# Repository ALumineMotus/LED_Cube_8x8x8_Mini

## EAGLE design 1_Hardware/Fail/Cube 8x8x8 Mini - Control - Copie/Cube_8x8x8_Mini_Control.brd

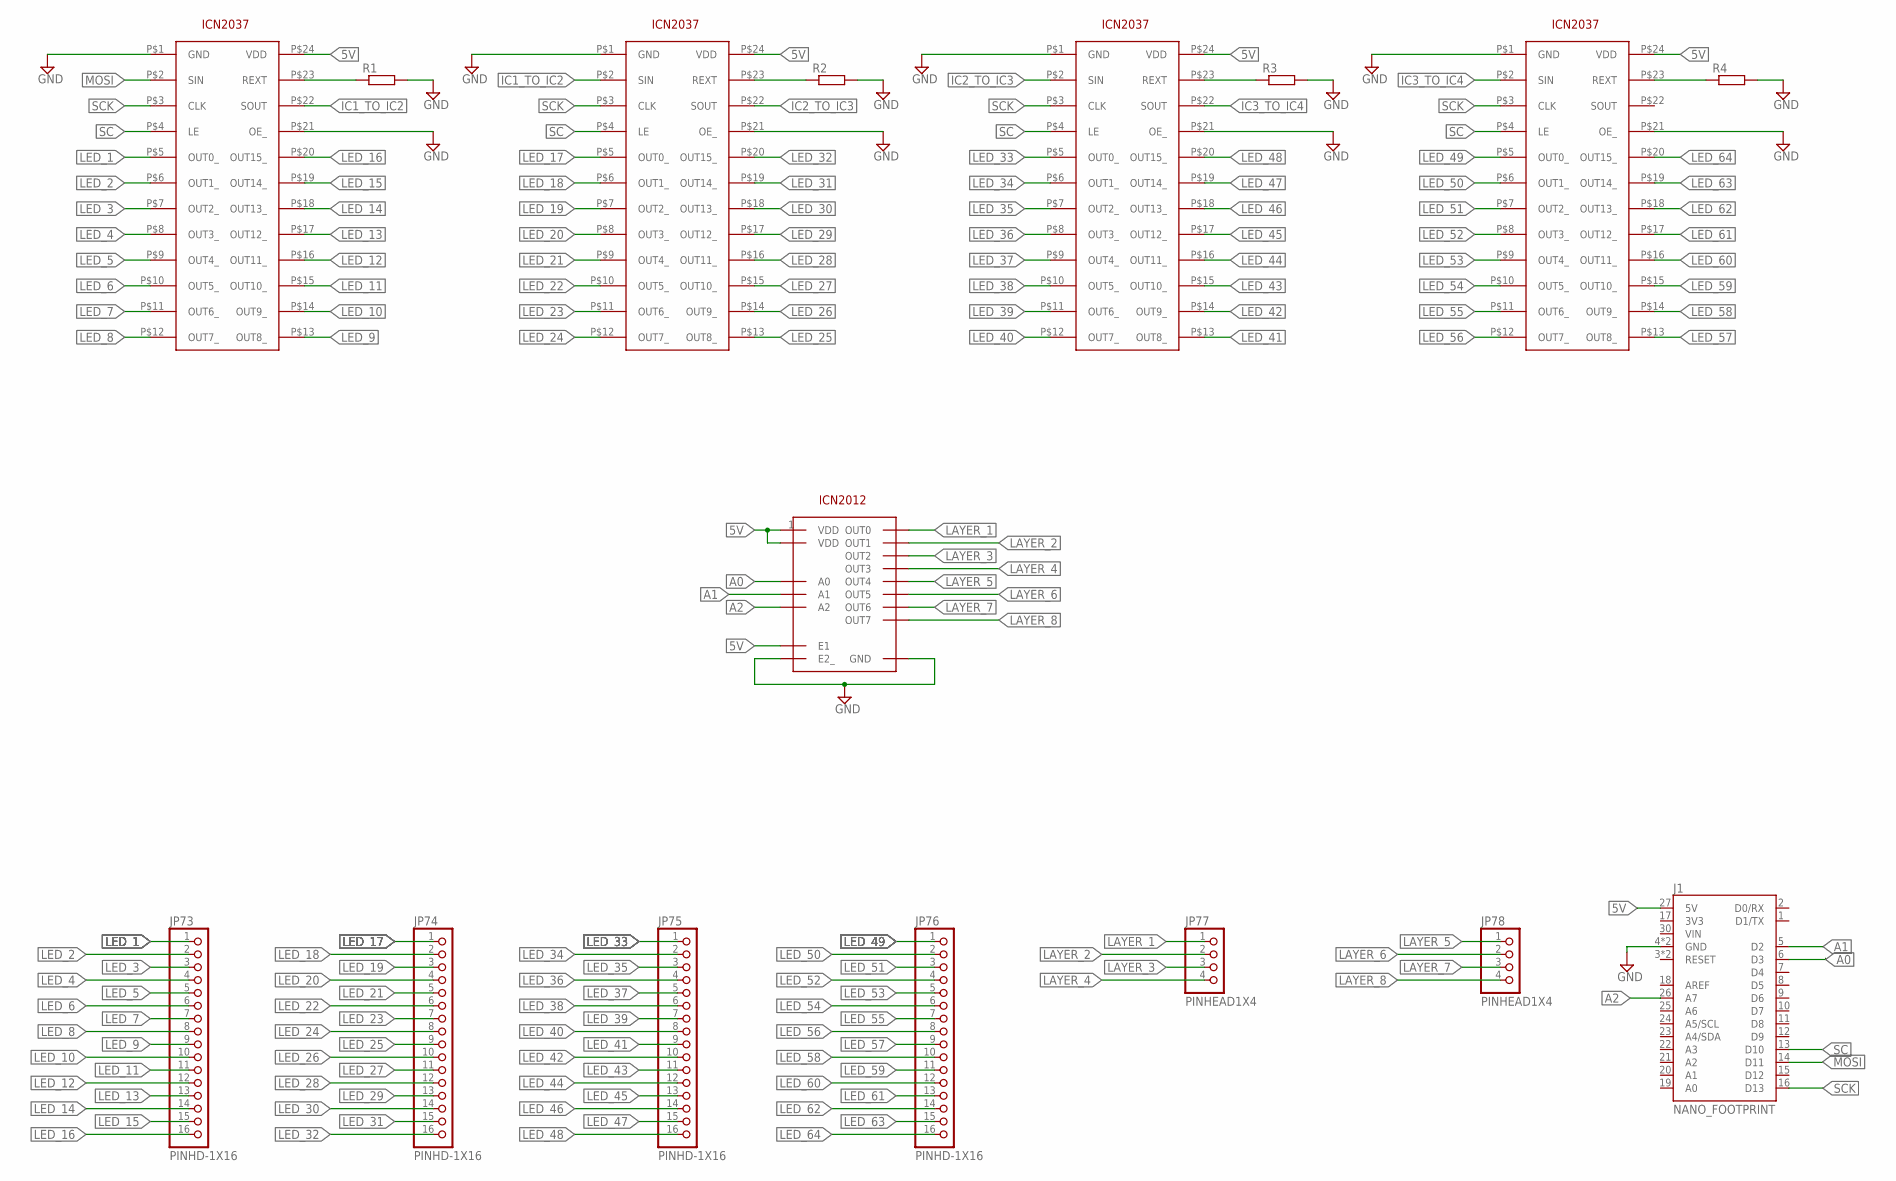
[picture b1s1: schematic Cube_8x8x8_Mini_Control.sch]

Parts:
J1: NANO_FOOTPRINT; NANO
JP73, JP74, JP75, JP76: PINHD-1X16; 2X16
JP77, JP78: PINHEAD1X4; 2X04
R1, R2, R3, R4: R-EU_R1206; R1206
U1, U2, U3, U4: ICN2037; SSOP24-P-150-0.635
U5: ICN2012; SOP16

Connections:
5V: J1.27 (5V), U1.P$24 (VDD), U2.P$24 (VDD), U3.P$24 (VDD), U4.P$24 (VDD), U5.1 (VDD), U5.7 (E1), U5.9 (VDD)
A0: J1.6 (D3), U5.15 (A0)
A1: J1.5 (D2), U5.16 (A1)
A2: J1.26 (A7), U5.2 (A2)
GND: J1.4 (GND), J1.29 (GND), R1.2, R2.2, R3.2, R4.2, U1.P$1 (GND), U1.P$21 (OE_), U2.P$1 (GND), U2.P$21 (OE_), U3.P$1 (GND), U3.P$21 (OE_), U4.P$1 (GND), U4.P$21 (OE_), U5.8 (GND), U5.10 (E2_)
IC1_TO_IC2: U1.P$22 (SOUT), U2.P$2 (SIN)
IC2_TO_IC3: U2.P$22 (SOUT), U3.P$2 (SIN)
IC3_TO_IC4: U3.P$22 (SOUT), U4.P$2 (SIN)
LAYER_1: JP77.1, U5.3 (OUT0)
LAYER_2: JP77.2, U5.4 (OUT1)
LAYER_3: JP77.3, U5.5 (OUT2)
LAYER_4: JP77.4, U5.6 (OUT3)
LAYER_5: JP78.1, U5.11 (OUT4)
LAYER_6: JP78.2, U5.12 (OUT5)
LAYER_7: JP78.3, U5.13 (OUT6)
LAYER_8: JP78.4, U5.14 (OUT7)
LED_1: JP73.1, U1.P$5 (OUT0_)
LED_2: JP73.2, U1.P$6 (OUT1_)
LED_3: JP73.3, U1.P$7 (OUT2_)
LED_4: JP73.4, U1.P$8 (OUT3_)
LED_5: JP73.5, U1.P$9 (OUT4_)
LED_6: JP73.6, U1.P$10 (OUT5_)
LED_7: JP73.7, U1.P$11 (OUT6_)
LED_8: JP73.8, U1.P$12 (OUT7_)
LED_9: JP73.9, U1.P$13 (OUT8_)
LED_10: JP73.10, U1.P$14 (OUT9_)
LED_11: JP73.11, U1.P$15 (OUT10_)
LED_12: JP73.12, U1.P$16 (OUT11_)
LED_13: JP73.13, U1.P$17 (OUT12_)
LED_14: JP73.14, U1.P$18 (OUT13_)
LED_15: JP73.15, U1.P$19 (OUT14_)
LED_16: JP73.16, U1.P$20 (OUT15_)
LED_17: JP74.1, U2.P$5 (OUT0_)
LED_18: JP74.2, U2.P$6 (OUT1_)
LED_19: JP74.3, U2.P$7 (OUT2_)
LED_20: JP74.4, U2.P$8 (OUT3_)
LED_21: JP74.5, U2.P$9 (OUT4_)
LED_22: JP74.6, U2.P$10 (OUT5_)
LED_23: JP74.7, U2.P$11 (OUT6_)
LED_24: JP74.8, U2.P$12 (OUT7_)
LED_25: JP74.9, U2.P$13 (OUT8_)
LED_26: JP74.10, U2.P$14 (OUT9_)
LED_27: JP74.11, U2.P$15 (OUT10_)
LED_28: JP74.12, U2.P$16 (OUT11_)
LED_29: JP74.13, U2.P$17 (OUT12_)
LED_30: JP74.14, U2.P$18 (OUT13_)
LED_31: JP74.15, U2.P$19 (OUT14_)
LED_32: JP74.16, U2.P$20 (OUT15_)
LED_33: JP75.1, U3.P$5 (OUT0_)
LED_34: JP75.2, U3.P$6 (OUT1_)
LED_35: JP75.3, U3.P$7 (OUT2_)
LED_36: JP75.4, U3.P$8 (OUT3_)
LED_37: JP75.5, U3.P$9 (OUT4_)
LED_38: JP75.6, U3.P$10 (OUT5_)
LED_39: JP75.7, U3.P$11 (OUT6_)
LED_40: JP75.8, U3.P$12 (OUT7_)
LED_41: JP75.9, U3.P$13 (OUT8_)
LED_42: JP75.10, U3.P$14 (OUT9_)
LED_43: JP75.11, U3.P$15 (OUT10_)
LED_44: JP75.12, U3.P$16 (OUT11_)
LED_45: JP75.13, U3.P$17 (OUT12_)
LED_46: JP75.14, U3.P$18 (OUT13_)
LED_47: JP75.15, U3.P$19 (OUT14_)
LED_48: JP75.16, U3.P$20 (OUT15_)
LED_49: JP76.1, U4.P$5 (OUT0_)
LED_50: JP76.2, U4.P$6 (OUT1_)
LED_51: JP76.3, U4.P$7 (OUT2_)
LED_52: JP76.4, U4.P$8 (OUT3_)
LED_53: JP76.5, U4.P$9 (OUT4_)
LED_54: JP76.6, U4.P$10 (OUT5_)
LED_55: JP76.7, U4.P$11 (OUT6_)
LED_56: JP76.8, U4.P$12 (OUT7_)
LED_57: JP76.9, U4.P$13 (OUT8_)
LED_58: JP76.10, U4.P$14 (OUT9_)
LED_59: JP76.11, U4.P$15 (OUT10_)
LED_60: JP76.12, U4.P$16 (OUT11_)
LED_61: JP76.13, U4.P$17 (OUT12_)
LED_62: JP76.14, U4.P$18 (OUT13_)
LED_63: JP76.15, U4.P$19 (OUT14_)
LED_64: JP76.16, U4.P$20 (OUT15_)
MOSI: J1.14 (D11), U1.P$2 (SIN)
unnamed: R1.1, U1.P$23 (REXT)
unnamed: R2.1, U2.P$23 (REXT)
unnamed: R3.1, U3.P$23 (REXT)
unnamed: R4.1, U4.P$23 (REXT)
SC: J1.13 (D10), U1.P$4 (LE), U2.P$4 (LE), U3.P$4 (LE), U4.P$4 (LE)
SCK: J1.16 (D13), U1.P$3 (CLK), U2.P$3 (CLK), U3.P$3 (CLK), U4.P$3 (CLK)

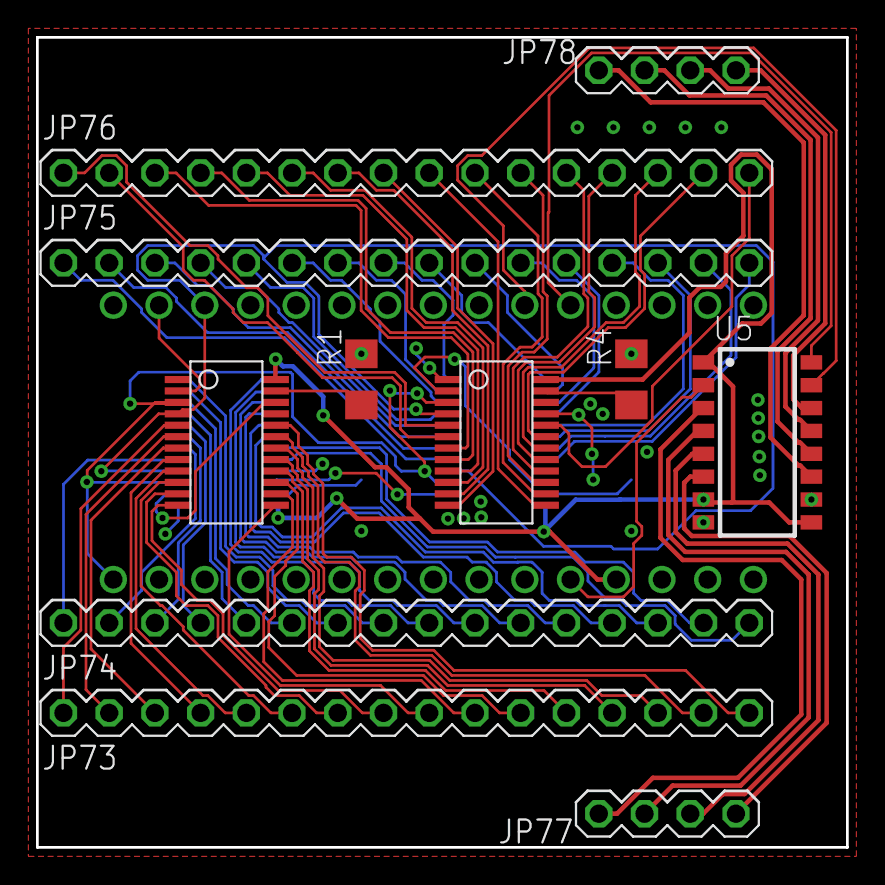
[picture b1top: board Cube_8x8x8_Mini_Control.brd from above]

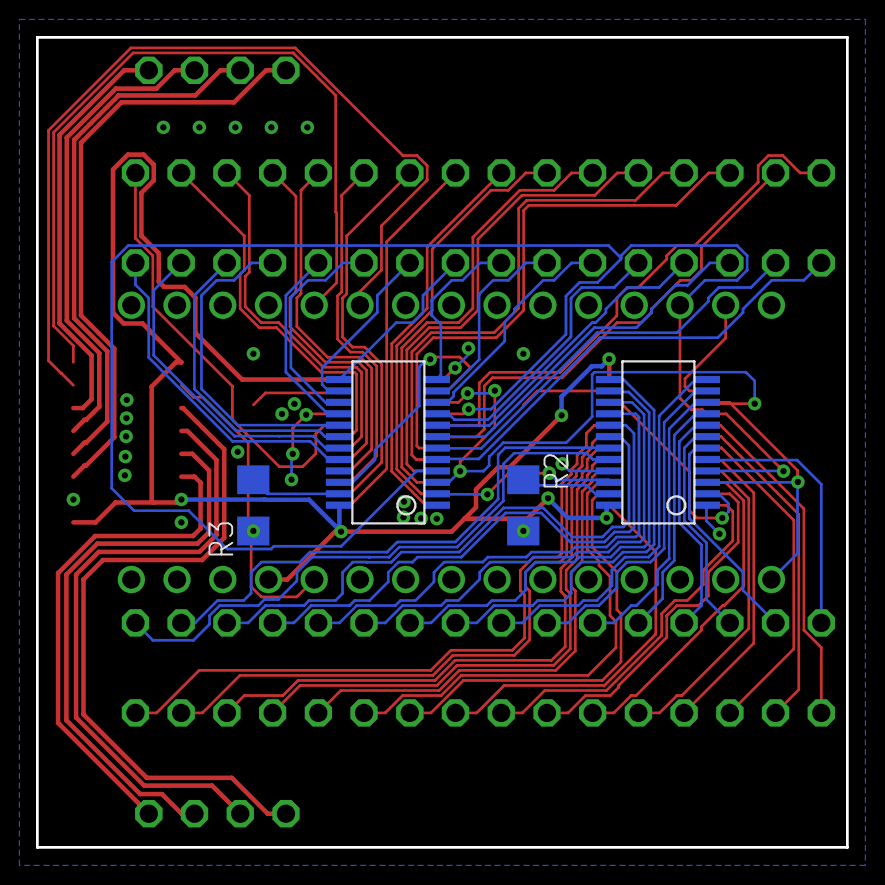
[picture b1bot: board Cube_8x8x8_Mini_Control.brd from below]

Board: 2 copper layers, 45.0 x 45.0 mm, 16 parts (4 on the bottom side), 87 nets.

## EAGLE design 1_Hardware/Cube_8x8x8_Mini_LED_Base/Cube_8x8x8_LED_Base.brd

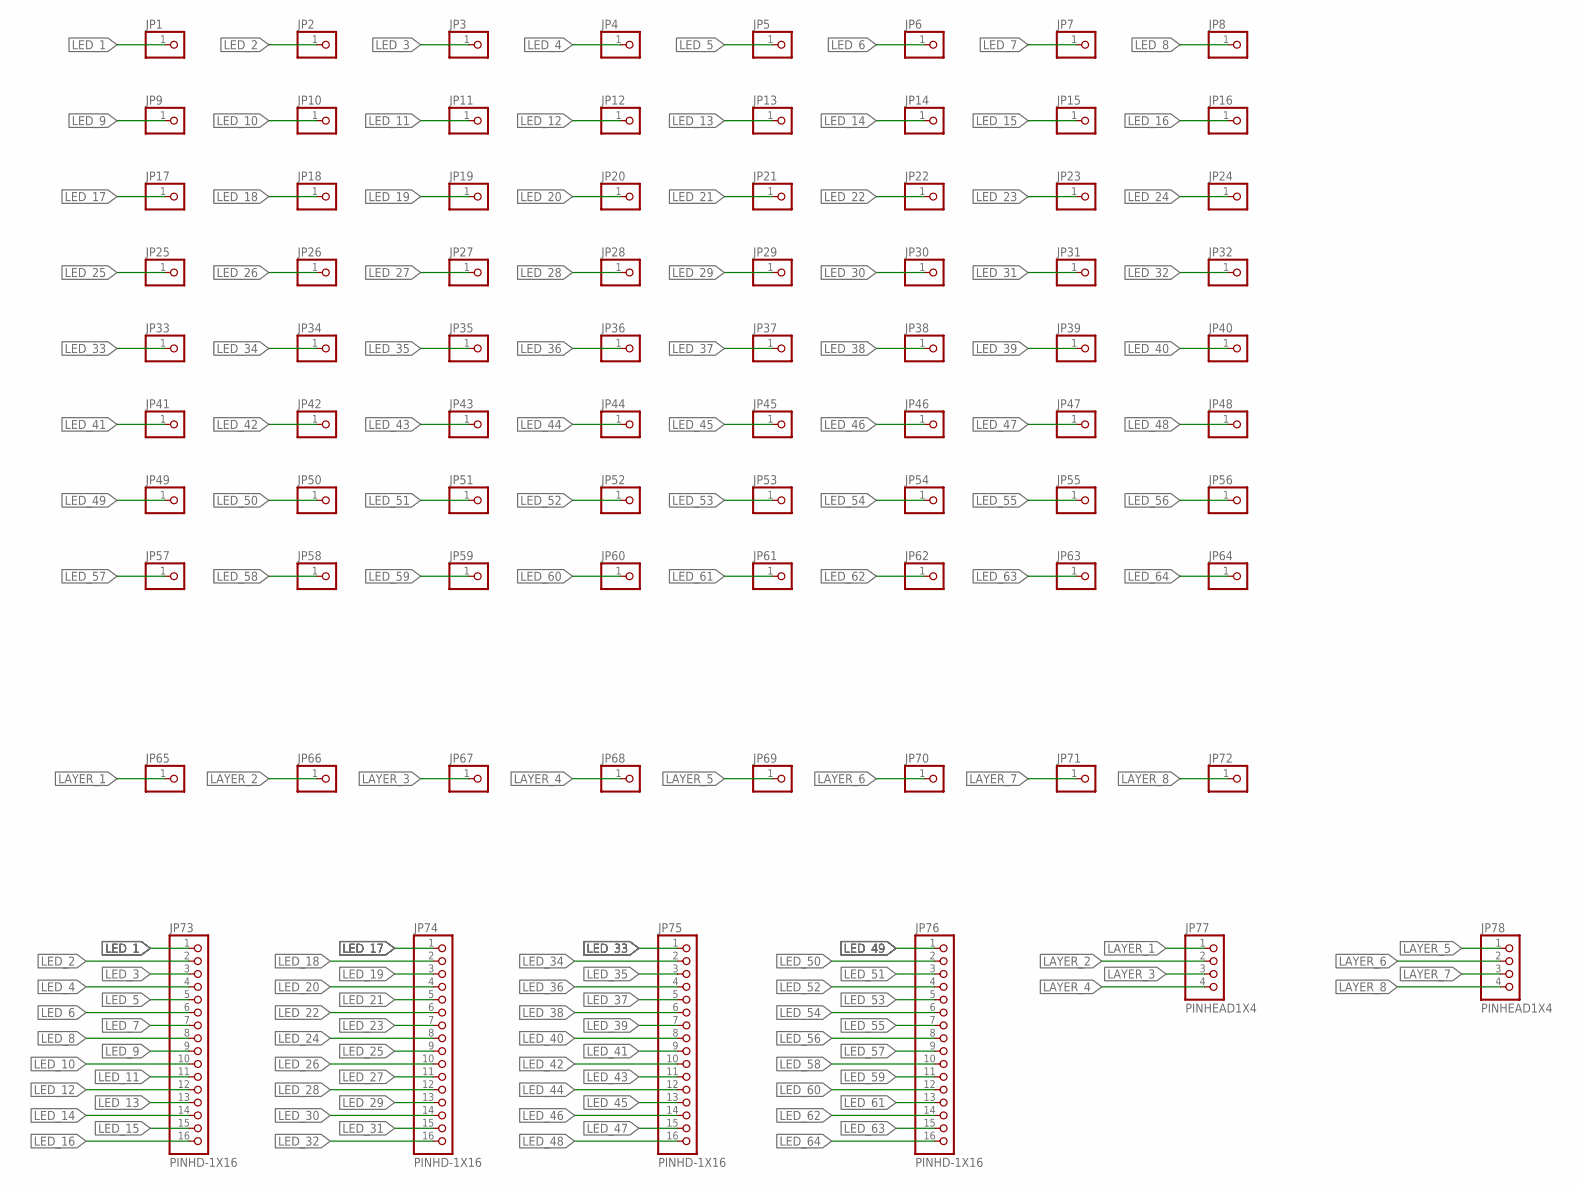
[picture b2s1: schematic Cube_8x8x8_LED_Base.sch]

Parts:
JP1, JP2, JP3, JP4, JP5, JP6, JP7, JP8, JP9, JP10, JP11, JP12, JP13, JP14, JP15, JP16, JP17, JP18, JP19, JP20, JP21, JP22, JP23, JP24, JP25, JP26, JP27, JP28, JP29, JP30, JP31, JP32, JP33, JP34, JP35, JP36, JP37, JP38, JP39, JP40, JP41, JP42, JP43, JP44, JP45, JP46, JP47, JP48, JP49, JP50, JP51, JP52, JP53, JP54, JP55, JP56, JP57, JP58, JP59, JP60, JP61, JP62, JP63, JP64, JP65, JP66, JP67, JP68, JP69, JP70, JP71, JP72: PINHD-1X1; 1X01
JP73, JP74, JP75, JP76: PINHD-1X16; 2X16
JP77, JP78: PINHEAD1X4; 2X04

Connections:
LAYER_1: JP65.1, JP77.1
LAYER_2: JP66.1, JP77.2
LAYER_3: JP67.1, JP77.3
LAYER_4: JP68.1, JP77.4
LAYER_5: JP69.1, JP78.1
LAYER_6: JP70.1, JP78.2
LAYER_7: JP71.1, JP78.3
LAYER_8: JP72.1, JP78.4
LED_1: JP1.1, JP73.1
LED_2: JP2.1, JP73.2
LED_3: JP3.1, JP73.3
LED_4: JP4.1, JP73.4
LED_5: JP5.1, JP73.5
LED_6: JP6.1, JP73.6
LED_7: JP7.1, JP73.7
LED_8: JP8.1, JP73.8
LED_9: JP9.1, JP73.9
LED_10: JP10.1, JP73.10
LED_11: JP11.1, JP73.11
LED_12: JP12.1, JP73.12
LED_13: JP13.1, JP73.13
LED_14: JP14.1, JP73.14
LED_15: JP15.1, JP73.15
LED_16: JP16.1, JP73.16
LED_17: JP17.1, JP74.1
LED_18: JP18.1, JP74.2
LED_19: JP19.1, JP74.3
LED_20: JP20.1, JP74.4
LED_21: JP21.1, JP74.5
LED_22: JP22.1, JP74.6
LED_23: JP23.1, JP74.7
LED_24: JP24.1, JP74.8
LED_25: JP25.1, JP74.9
LED_26: JP26.1, JP74.10
LED_27: JP27.1, JP74.11
LED_28: JP28.1, JP74.12
LED_29: JP29.1, JP74.13
LED_30: JP30.1, JP74.14
LED_31: JP31.1, JP74.15
LED_32: JP32.1, JP74.16
LED_33: JP33.1, JP75.1
LED_34: JP34.1, JP75.2
LED_35: JP35.1, JP75.3
LED_36: JP36.1, JP75.4
LED_37: JP37.1, JP75.5
LED_38: JP38.1, JP75.6
LED_39: JP39.1, JP75.7
LED_40: JP40.1, JP75.8
LED_41: JP41.1, JP75.9
LED_42: JP42.1, JP75.10
LED_43: JP43.1, JP75.11
LED_44: JP44.1, JP75.12
LED_45: JP45.1, JP75.13
LED_46: JP46.1, JP75.14
LED_47: JP47.1, JP75.15
LED_48: JP48.1, JP75.16
LED_49: JP49.1, JP76.1
LED_50: JP50.1, JP76.2
LED_51: JP51.1, JP76.3
LED_52: JP52.1, JP76.4
LED_53: JP53.1, JP76.5
LED_54: JP54.1, JP76.6
LED_55: JP55.1, JP76.7
LED_56: JP56.1, JP76.8
LED_57: JP57.1, JP76.9
LED_58: JP58.1, JP76.10
LED_59: JP59.1, JP76.11
LED_60: JP60.1, JP76.12
LED_61: JP61.1, JP76.13
LED_62: JP62.1, JP76.14
LED_63: JP63.1, JP76.15
LED_64: JP64.1, JP76.16

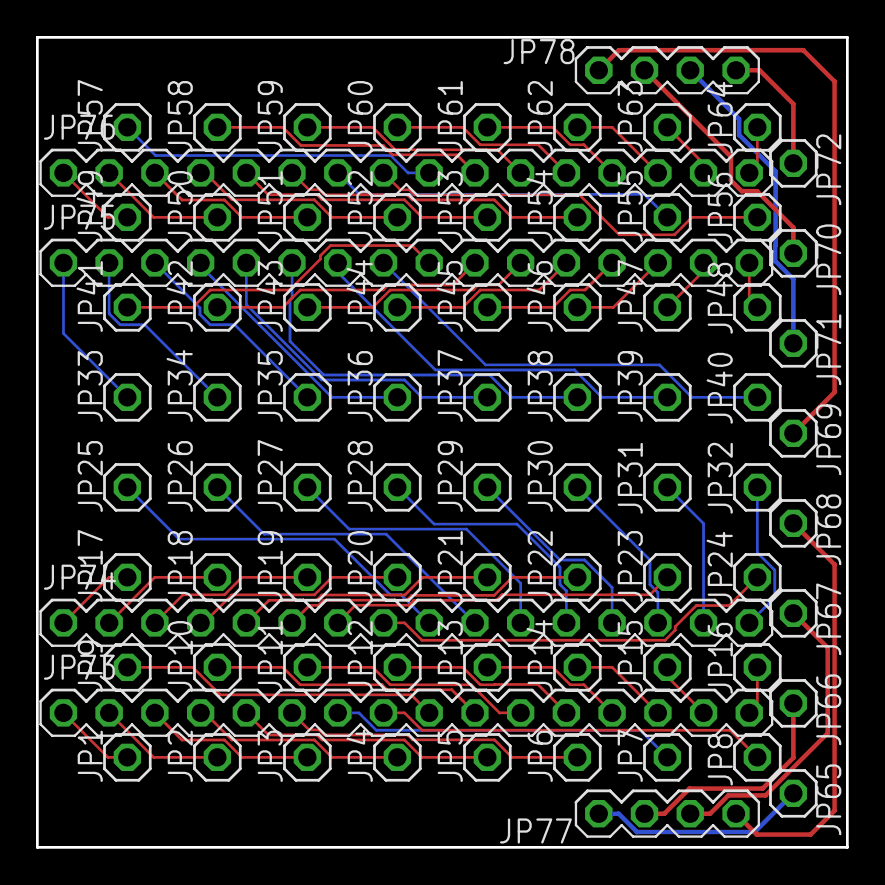
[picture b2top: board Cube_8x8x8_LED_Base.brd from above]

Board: 2 copper layers, 45.0 x 45.0 mm, 78 parts (0 on the bottom side), 72 nets.

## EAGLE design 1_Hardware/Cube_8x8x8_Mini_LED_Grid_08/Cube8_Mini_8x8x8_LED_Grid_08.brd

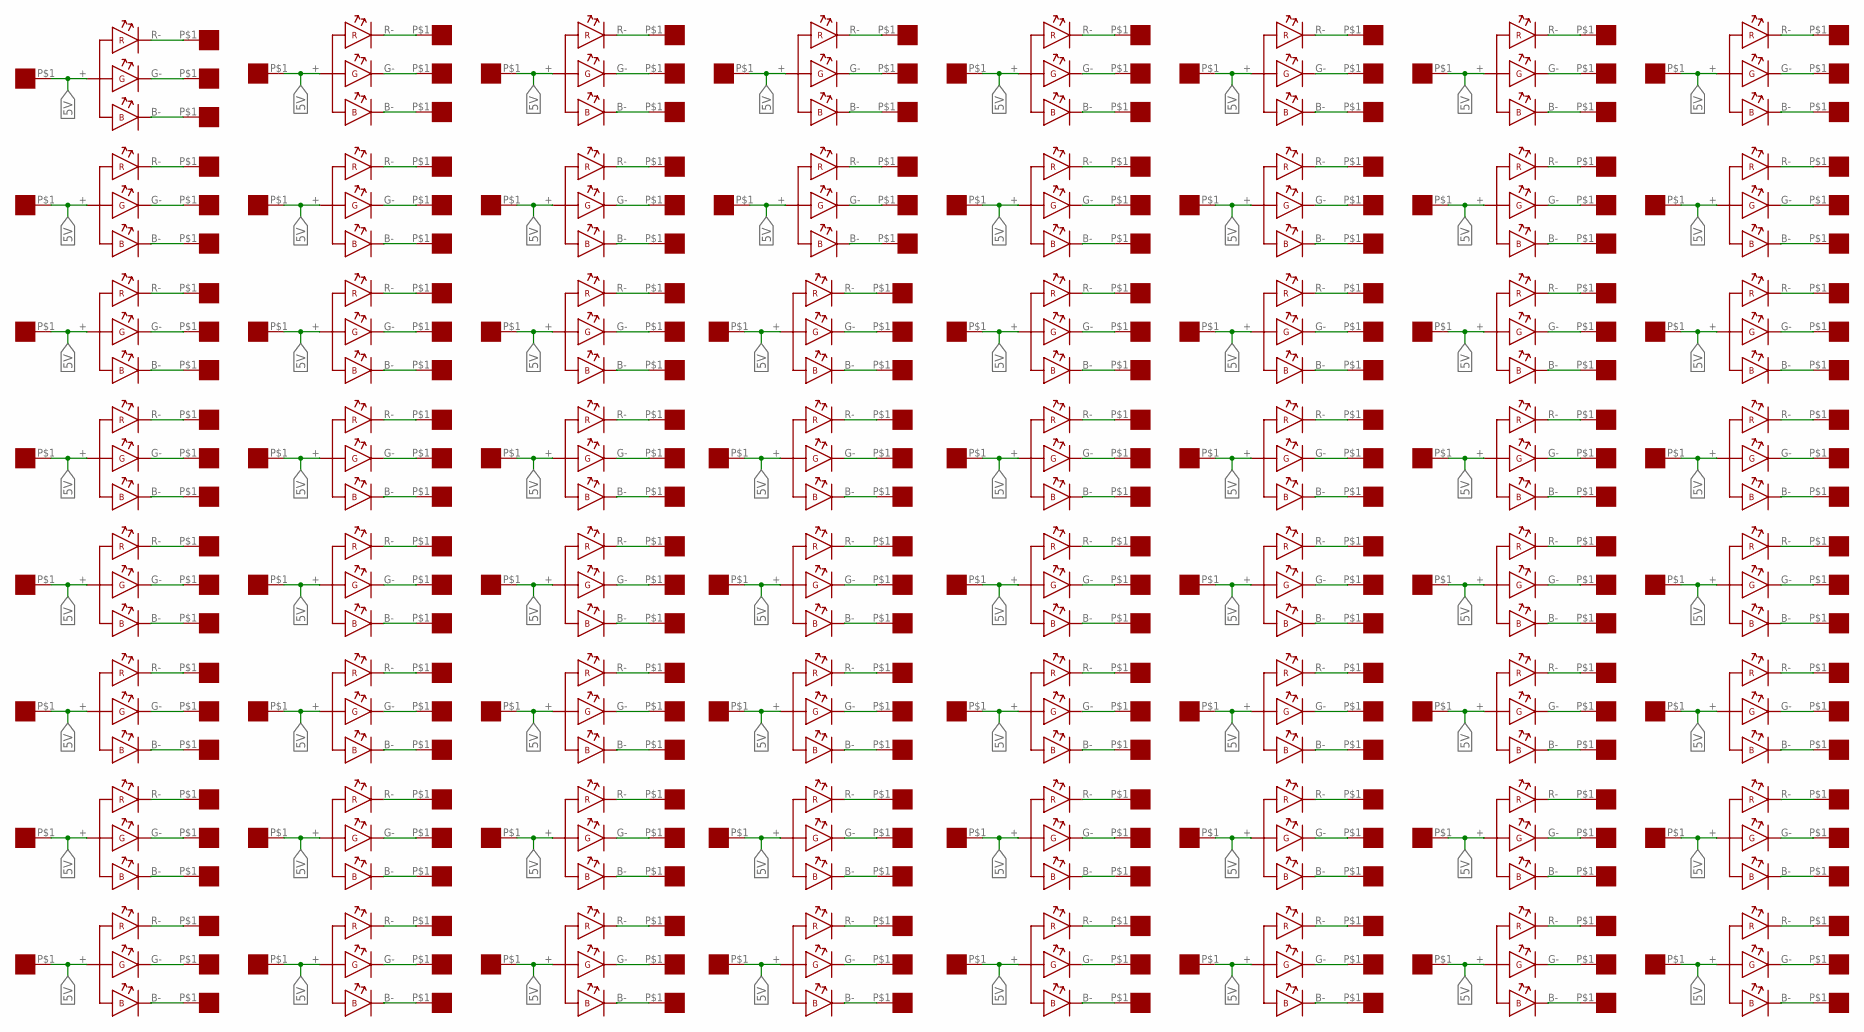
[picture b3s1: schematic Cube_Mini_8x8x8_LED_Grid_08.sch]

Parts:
5V$1, 5V$2, 5V$3, 5V$4, 5V$5, 5V$6, 5V$7, 5V$8, 5V$9, 5V$10, 5V$11, 5V$12, 5V$13, 5V$14, 5V$15, 5V$16, 5V$17, 5V$18, 5V$19, 5V$20, 5V$21, 5V$22, 5V$23, 5V$24, 5V$25, 5V$26, 5V$27, 5V$28, 5V$29, 5V$30, 5V$31, 5V$32, 5V$33, 5V$34, 5V$35, 5V$36, 5V$37, 5V$38, 5V$39, 5V$40, 5V$41, 5V$42, 5V$43, 5V$44, 5V$45, 5V$46, 5V$47, 5V$48, 5V$49, 5V$50, 5V$51, 5V$52, 5V$53, 5V$54, 5V$55, 5V$56, 5V$57, 5V$58, 5V$59, 5V$60, 5V$61, 5V$62, 5V$63, 5V$64: 05X08PAD
B$1, B$2, B$3, B$4, B$5, B$6, B$7, B$8, B$9, B$10, B$11, B$12, B$13, B$14, B$15, B$16, B$17, B$18, B$19, B$20, B$21, B$22, B$23, B$24, B$25, B$26, B$27, B$28, B$29, B$30, B$31, B$32, B$33, B$34, B$35, B$36, B$37, B$38, B$39, B$40, B$41, B$42, B$43, B$44, B$45, B$46, B$47, B$48, B$49, B$50, B$51, B$52, B$53, B$54, B$55, B$56, B$57, B$58, B$59, B$60, B$61, B$62, B$63, B$64: 05X08PAD
G$1, G$2, G$3, G$4, G$5, G$6, G$7, G$8, G$9, G$10, G$11, G$12, G$13, G$14, G$15, G$16, G$17, G$18, G$19, G$20, G$21, G$22, G$23, G$24, G$25, G$26, G$27, G$28, G$29, G$30, G$31, G$32, G$33, G$34, G$35, G$36, G$37, G$38, G$39, G$40, G$41, G$42, G$43, G$44, G$45, G$46, G$47, G$48, G$49, G$50, G$51, G$52, G$53, G$54, G$55, G$56, G$57, G$58, G$59, G$60, G$61, G$62, G$63, G$64: 05X08PAD
R$1, R$2, R$3, R$4, R$5, R$6, R$7, R$8, R$9, R$10, R$11, R$12, R$13, R$14, R$15, R$16, R$17, R$18, R$19, R$20, R$21, R$22, R$23, R$24, R$25, R$26, R$27, R$28, R$29, R$30, R$31, R$32, R$33, R$34, R$35, R$36, R$37, R$38, R$39, R$40, R$41, R$42, R$43, R$44, R$45, R$46, R$47, R$48, R$49, R$50, R$51, R$52, R$53, R$54, R$55, R$56, R$57, R$58, R$59, R$60, R$61, R$62, R$63, R$64: 05X08PAD
U$1, U$2, U$3, U$4, U$5, U$6, U$7, U$8, U$9, U$10, U$11, U$12, U$13, U$14, U$15, U$16, U$17, U$18, U$19, U$20, U$21, U$22, U$23, U$24, U$25, U$26, U$27, U$28, U$29, U$30, U$31, U$32, U$33, U$34, U$35, U$36, U$37, U$38, U$39, U$40, U$41, U$42, U$43, U$44, U$45, U$46, U$47, U$48, U$49, U$50, U$51, U$52, U$53, U$54, U$55, U$56, U$57, U$58, U$59, U$60, U$61, U$62, U$63, U$64: B1010RGBT

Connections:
5V: 5V$1.P$1, 5V$2.P$1, 5V$3.P$1, 5V$4.P$1, 5V$5.P$1, 5V$6.P$1, 5V$7.P$1, 5V$8.P$1, 5V$9.P$1, 5V$10.P$1, 5V$11.P$1, 5V$12.P$1, 5V$13.P$1, 5V$14.P$1, 5V$15.P$1, 5V$16.P$1, 5V$17.P$1, 5V$18.P$1, 5V$19.P$1, 5V$20.P$1, 5V$21.P$1, 5V$22.P$1, 5V$23.P$1, 5V$24.P$1, 5V$25.P$1, 5V$26.P$1, 5V$27.P$1, 5V$28.P$1, 5V$29.P$1, 5V$30.P$1, 5V$31.P$1, 5V$32.P$1, 5V$33.P$1, 5V$34.P$1, 5V$35.P$1, 5V$36.P$1, 5V$37.P$1, 5V$38.P$1, 5V$39.P$1, 5V$40.P$1, 5V$41.P$1, 5V$42.P$1, 5V$43.P$1, 5V$44.P$1, 5V$45.P$1, 5V$46.P$1, 5V$47.P$1, 5V$48.P$1, 5V$49.P$1, 5V$50.P$1, 5V$51.P$1, 5V$52.P$1, 5V$53.P$1, 5V$54.P$1, 5V$55.P$1, 5V$56.P$1, 5V$57.P$1, 5V$58.P$1, 5V$59.P$1, 5V$60.P$1, 5V$61.P$1, 5V$62.P$1, 5V$63.P$1, 5V$64.P$1, U$1.+, U$2.+, U$3.+, U$4.+, U$5.+, U$6.+, U$7.+, U$8.+, U$9.+, U$10.+, U$11.+, U$12.+, U$13.+, U$14.+, U$15.+, U$16.+, U$17.+, U$18.+, U$19.+, U$20.+, U$21.+, U$22.+, U$23.+, U$24.+, U$25.+, U$26.+, U$27.+, U$28.+, U$29.+, U$30.+, U$31.+, U$32.+, U$33.+, U$34.+, U$35.+, U$36.+, U$37.+, U$38.+, U$39.+, U$40.+, U$41.+, U$42.+, U$43.+, U$44.+, U$45.+, U$46.+, U$47.+, U$48.+, U$49.+, U$50.+, U$51.+, U$52.+, U$53.+, U$54.+, U$55.+, U$56.+, U$57.+, U$58.+, U$59.+, U$60.+, U$61.+, U$62.+, U$63.+, U$64.+
unnamed: R$1.P$1, U$1.R-
unnamed: G$1.P$1, U$1.G-
unnamed: B$1.P$1, U$1.B-
unnamed: R$2.P$1, U$2.R-
unnamed: G$2.P$1, U$2.G-
unnamed: B$2.P$1, U$2.B-
unnamed: R$3.P$1, U$3.R-
unnamed: G$3.P$1, U$3.G-
unnamed: B$3.P$1, U$3.B-
unnamed: R$5.P$1, U$5.R-
unnamed: G$5.P$1, U$5.G-
unnamed: B$5.P$1, U$5.B-
unnamed: R$4.P$1, U$4.R-
unnamed: G$4.P$1, U$4.G-
unnamed: B$4.P$1, U$4.B-
unnamed: R$7.P$1, U$7.R-
unnamed: G$7.P$1, U$7.G-
unnamed: B$7.P$1, U$7.B-
unnamed: R$6.P$1, U$6.R-
unnamed: G$6.P$1, U$6.G-
unnamed: B$6.P$1, U$6.B-
unnamed: R$9.P$1, U$9.R-
unnamed: G$9.P$1, U$9.G-
unnamed: B$9.P$1, U$9.B-
unnamed: R$8.P$1, U$8.R-
unnamed: G$8.P$1, U$8.G-
unnamed: B$8.P$1, U$8.B-
unnamed: R$11.P$1, U$11.R-
unnamed: G$11.P$1, U$11.G-
unnamed: B$11.P$1, U$11.B-
unnamed: R$10.P$1, U$10.R-
unnamed: G$10.P$1, U$10.G-
unnamed: B$10.P$1, U$10.B-
unnamed: R$12.P$1, U$12.R-
unnamed: G$12.P$1, U$12.G-
unnamed: B$12.P$1, U$12.B-
unnamed: R$13.P$1, U$13.R-
unnamed: G$13.P$1, U$13.G-
unnamed: B$13.P$1, U$13.B-
unnamed: R$14.P$1, U$14.R-
unnamed: G$14.P$1, U$14.G-
unnamed: B$14.P$1, U$14.B-
unnamed: R$15.P$1, U$15.R-
unnamed: G$15.P$1, U$15.G-
unnamed: B$15.P$1, U$15.B-
unnamed: R$16.P$1, U$16.R-
unnamed: G$16.P$1, U$16.G-
unnamed: B$16.P$1, U$16.B-
unnamed: R$17.P$1, U$17.R-
unnamed: G$17.P$1, U$17.G-
unnamed: B$17.P$1, U$17.B-
unnamed: R$18.P$1, U$18.R-
unnamed: G$18.P$1, U$18.G-
unnamed: B$18.P$1, U$18.B-
unnamed: R$19.P$1, U$19.R-
unnamed: G$19.P$1, U$19.G-
unnamed: B$19.P$1, U$19.B-
unnamed: R$20.P$1, U$20.R-
unnamed: G$20.P$1, U$20.G-
unnamed: B$20.P$1, U$20.B-
unnamed: R$21.P$1, U$21.R-
unnamed: G$21.P$1, U$21.G-
unnamed: B$21.P$1, U$21.B-
unnamed: R$22.P$1, U$22.R-
unnamed: G$22.P$1, U$22.G-
unnamed: B$22.P$1, U$22.B-
unnamed: R$23.P$1, U$23.R-
unnamed: G$23.P$1, U$23.G-
unnamed: B$23.P$1, U$23.B-
unnamed: R$24.P$1, U$24.R-
unnamed: G$24.P$1, U$24.G-
unnamed: B$24.P$1, U$24.B-
unnamed: R$25.P$1, U$25.R-
unnamed: G$25.P$1, U$25.G-
unnamed: B$25.P$1, U$25.B-
unnamed: R$26.P$1, U$26.R-
unnamed: G$26.P$1, U$26.G-
unnamed: B$26.P$1, U$26.B-
unnamed: R$27.P$1, U$27.R-
unnamed: G$27.P$1, U$27.G-
unnamed: B$27.P$1, U$27.B-
unnamed: R$28.P$1, U$28.R-
unnamed: G$28.P$1, U$28.G-
unnamed: B$28.P$1, U$28.B-
unnamed: R$29.P$1, U$29.R-
unnamed: G$29.P$1, U$29.G-
unnamed: B$29.P$1, U$29.B-
unnamed: R$30.P$1, U$30.R-
unnamed: G$30.P$1, U$30.G-
unnamed: B$30.P$1, U$30.B-
unnamed: R$31.P$1, U$31.R-
unnamed: G$31.P$1, U$31.G-
unnamed: B$31.P$1, U$31.B-
unnamed: R$32.P$1, U$32.R-
unnamed: G$32.P$1, U$32.G-
unnamed: B$32.P$1, U$32.B-
unnamed: R$33.P$1, U$33.R-
unnamed: G$33.P$1, U$33.G-
unnamed: B$33.P$1, U$33.B-
unnamed: R$34.P$1, U$34.R-
unnamed: G$34.P$1, U$34.G-
unnamed: B$34.P$1, U$34.B-
unnamed: R$35.P$1, U$35.R-
unnamed: G$35.P$1, U$35.G-
unnamed: B$35.P$1, U$35.B-
unnamed: R$36.P$1, U$36.R-
unnamed: G$36.P$1, U$36.G-
unnamed: B$36.P$1, U$36.B-
unnamed: R$38.P$1, U$38.R-
unnamed: G$38.P$1, U$38.G-
unnamed: B$38.P$1, U$38.B-
unnamed: R$37.P$1, U$37.R-
unnamed: G$37.P$1, U$37.G-
unnamed: B$37.P$1, U$37.B-
unnamed: R$39.P$1, U$39.R-
unnamed: G$39.P$1, U$39.G-
unnamed: B$39.P$1, U$39.B-
unnamed: R$40.P$1, U$40.R-
unnamed: G$40.P$1, U$40.G-
unnamed: B$40.P$1, U$40.B-
unnamed: R$41.P$1, U$41.R-
unnamed: G$41.P$1, U$41.G-
unnamed: B$41.P$1, U$41.B-
unnamed: R$42.P$1, U$42.R-
unnamed: G$42.P$1, U$42.G-
unnamed: B$42.P$1, U$42.B-
unnamed: R$44.P$1, U$44.R-
unnamed: G$44.P$1, U$44.G-
unnamed: B$44.P$1, U$44.B-
unnamed: R$43.P$1, U$43.R-
unnamed: G$43.P$1, U$43.G-
unnamed: B$43.P$1, U$43.B-
unnamed: R$45.P$1, U$45.R-
unnamed: G$45.P$1, U$45.G-
unnamed: B$45.P$1, U$45.B-
unnamed: R$46.P$1, U$46.R-
unnamed: G$46.P$1, U$46.G-
unnamed: B$46.P$1, U$46.B-
unnamed: R$47.P$1, U$47.R-
unnamed: G$47.P$1, U$47.G-
unnamed: B$47.P$1, U$47.B-
unnamed: R$48.P$1, U$48.R-
unnamed: G$48.P$1, U$48.G-
unnamed: B$48.P$1, U$48.B-
unnamed: R$50.P$1, U$50.R-
unnamed: G$50.P$1, U$50.G-
unnamed: B$50.P$1, U$50.B-
unnamed: R$49.P$1, U$49.R-
unnamed: G$49.P$1, U$49.G-
unnamed: B$49.P$1, U$49.B-
unnamed: R$51.P$1, U$51.R-
unnamed: G$51.P$1, U$51.G-
unnamed: B$51.P$1, U$51.B-
unnamed: R$53.P$1, U$53.R-
unnamed: G$53.P$1, U$53.G-
unnamed: B$53.P$1, U$53.B-
unnamed: R$52.P$1, U$52.R-
unnamed: G$52.P$1, U$52.G-
unnamed: B$52.P$1, U$52.B-
unnamed: R$54.P$1, U$54.R-
unnamed: G$54.P$1, U$54.G-
unnamed: B$54.P$1, U$54.B-
unnamed: R$55.P$1, U$55.R-
unnamed: G$55.P$1, U$55.G-
unnamed: B$55.P$1, U$55.B-
unnamed: R$56.P$1, U$56.R-
unnamed: G$56.P$1, U$56.G-
unnamed: B$56.P$1, U$56.B-
unnamed: R$58.P$1, U$58.R-
unnamed: G$58.P$1, U$58.G-
unnamed: B$58.P$1, U$58.B-
unnamed: R$57.P$1, U$57.R-
unnamed: G$57.P$1, U$57.G-
unnamed: B$57.P$1, U$57.B-
unnamed: R$59.P$1, U$59.R-
unnamed: G$59.P$1, U$59.G-
unnamed: B$59.P$1, U$59.B-
unnamed: R$60.P$1, U$60.R-
unnamed: G$60.P$1, U$60.G-
unnamed: B$60.P$1, U$60.B-
unnamed: R$61.P$1, U$61.R-
unnamed: G$61.P$1, U$61.G-
unnamed: B$61.P$1, U$61.B-
unnamed: R$62.P$1, U$62.R-
unnamed: G$62.P$1, U$62.G-
unnamed: B$62.P$1, U$62.B-
unnamed: R$63.P$1, U$63.R-
unnamed: G$63.P$1, U$63.G-
unnamed: B$63.P$1, U$63.B-
unnamed: R$64.P$1, U$64.R-
unnamed: G$64.P$1, U$64.G-
unnamed: B$64.P$1, U$64.B-

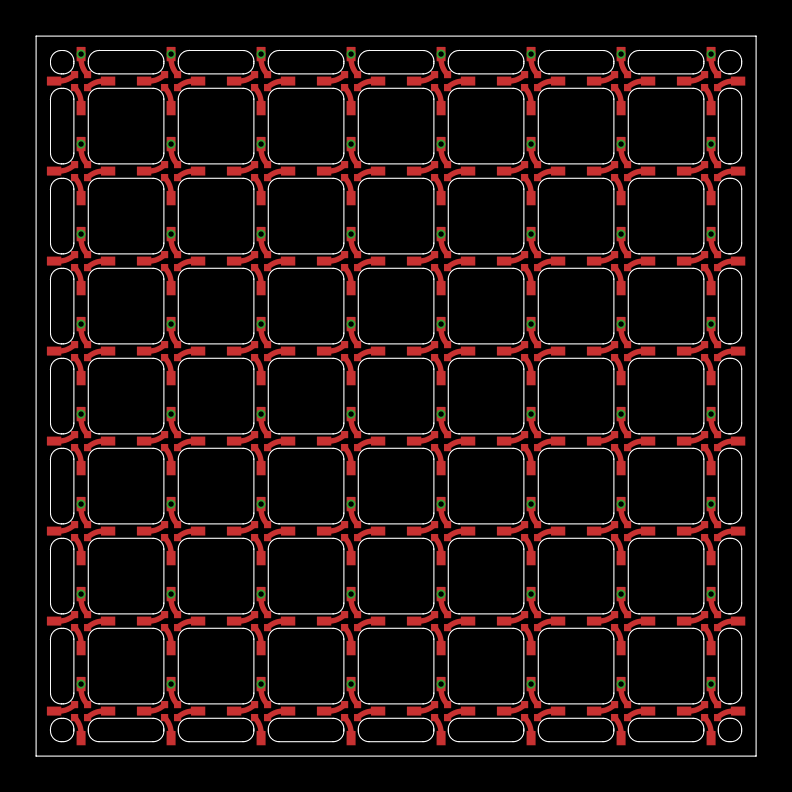
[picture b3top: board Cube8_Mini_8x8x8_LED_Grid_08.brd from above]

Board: 2 copper layers, 40.0 x 40.0 mm, 320 parts (0 on the bottom side), 193 nets.

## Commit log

2024-01-14 Add project
2024-05-30 Update board and components

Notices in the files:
parts and their libraries:
SparkFun-Boards: Licensing: Creative Commons ShareAlike 4.0 International - https://creativecommons.org/licenses/by-sa/4.0
